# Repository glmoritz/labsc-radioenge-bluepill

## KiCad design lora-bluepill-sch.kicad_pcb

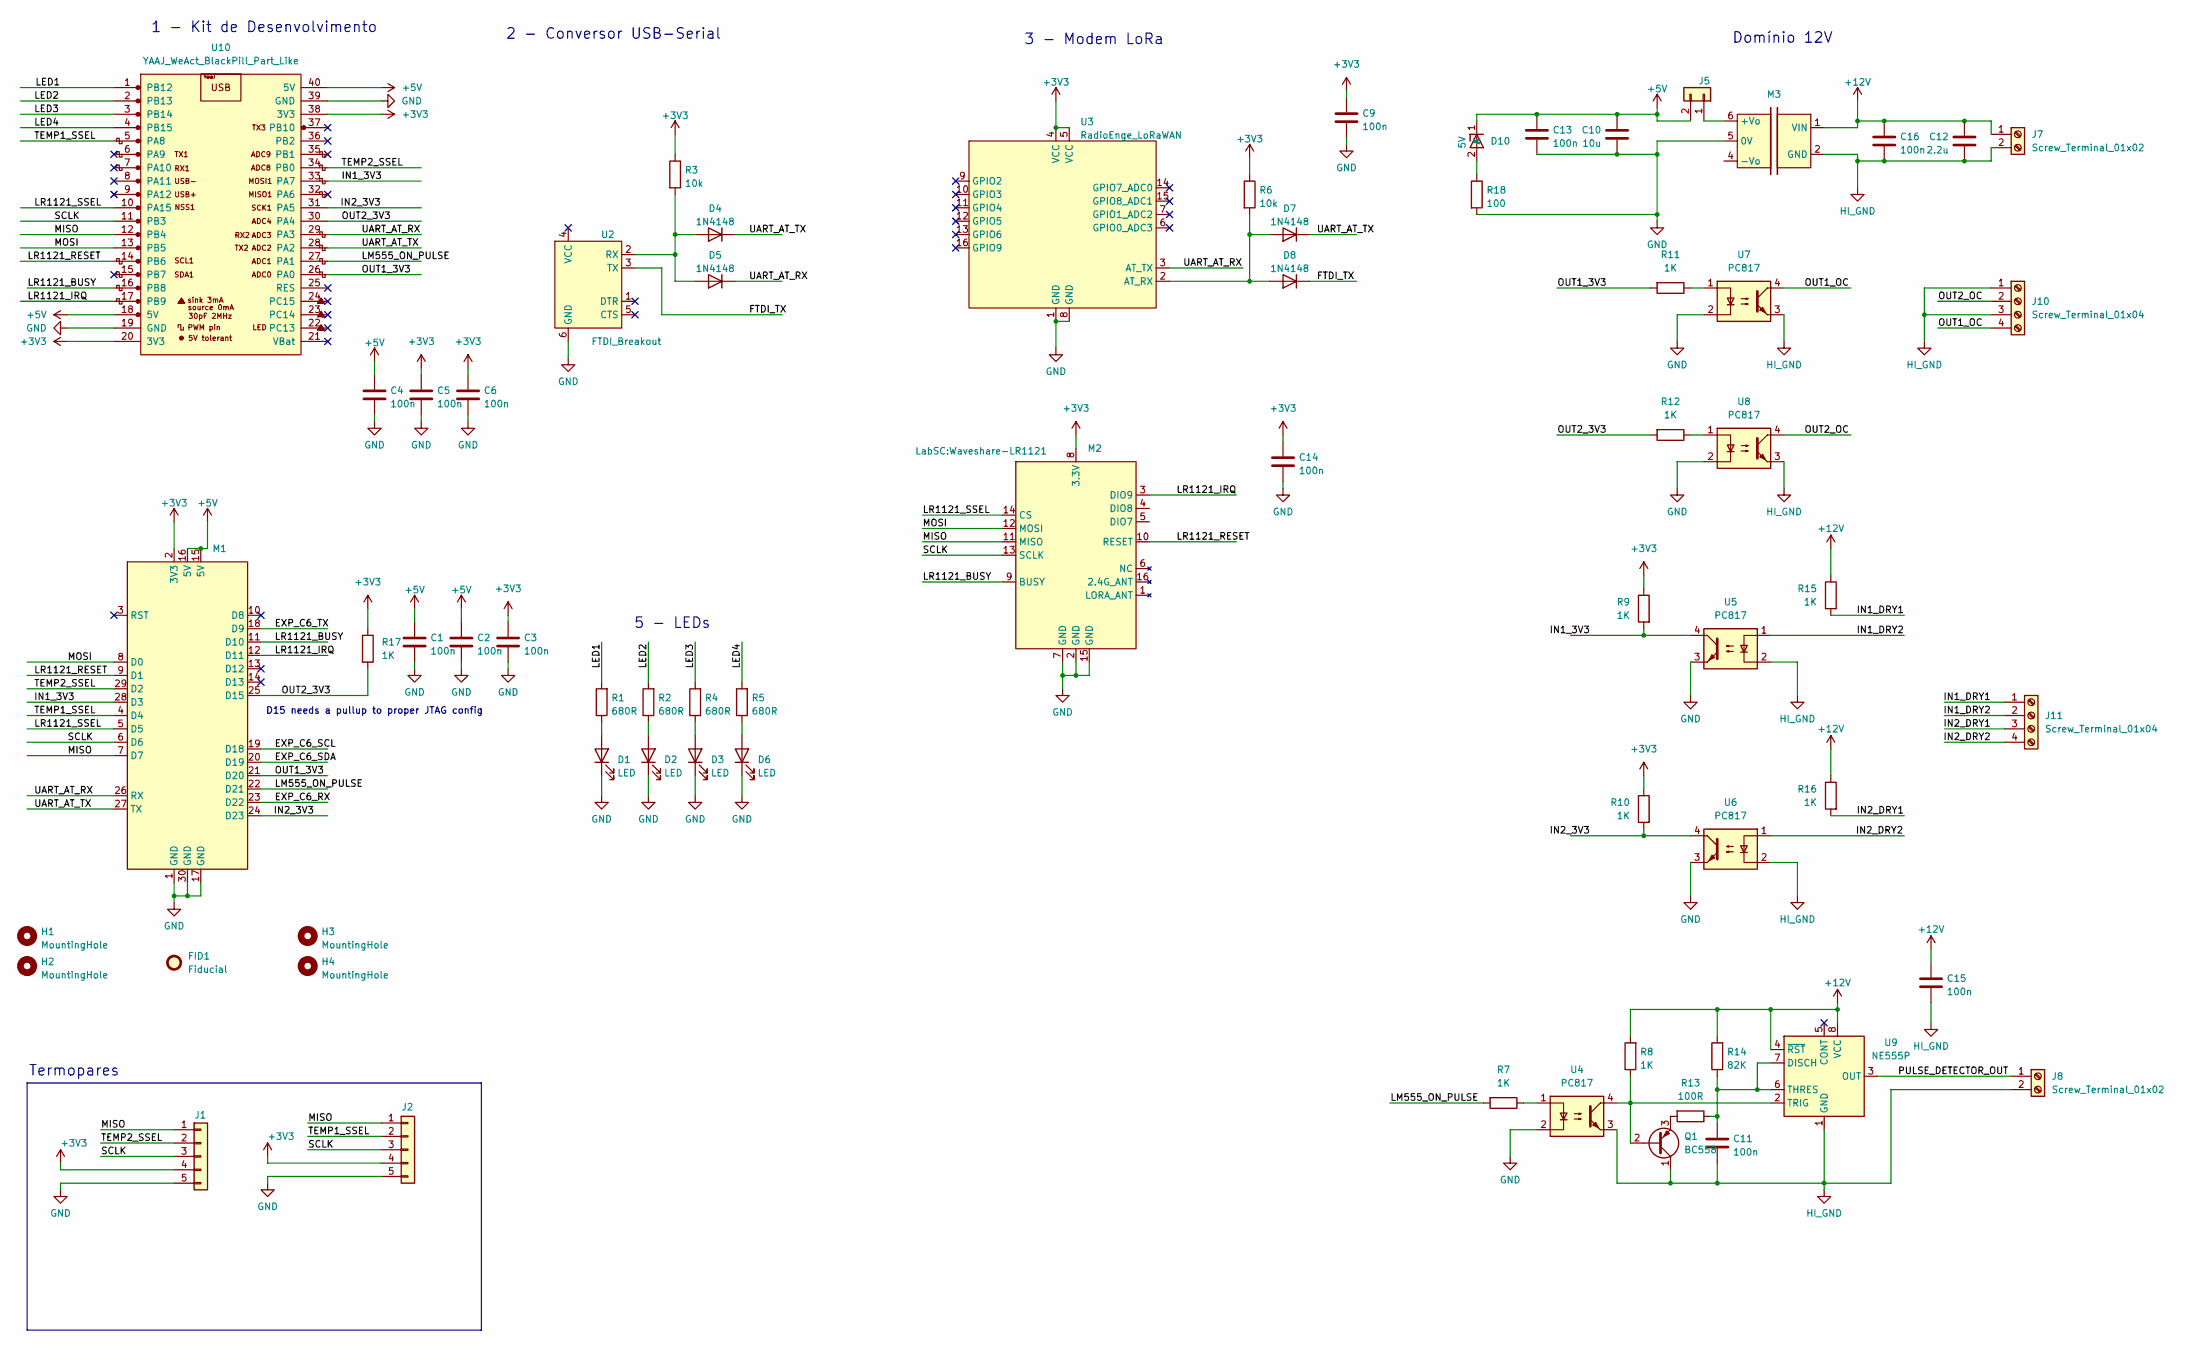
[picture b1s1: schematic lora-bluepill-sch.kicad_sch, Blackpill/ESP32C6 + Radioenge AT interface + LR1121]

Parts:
C1, C2, C3, C4, C5, C6, C9, C11, C13, C14, C15, C16: 100n; C_Disc_D6.0mm_W4.4mm_P5.00mm
C10: 10u; CP_Radial_D5.0mm_P2.50mm
C12: 2.2u; CP_Radial_D5.0mm_P2.50mm
D1, D2, D3, D6: LED; LED_D3.0mm
D4, D5, D7, D8: 1N4148; D_DO-35_SOD27_P7.62mm_Horizontal
D10: 5V; D_DO-35_SOD27_P7.62mm_Horizontal
FID1: Fiducial; labsc-logo
H1, H2, H3, H4: MountingHole; MountingHole_2.2mm_M2_DIN965
J1, J2: Conn_01x05; PinHeader_1x05_P2.54mm_Horizontal
J5: Conn_01x02; PinHeader_1x02_P2.54mm_Vertical
J7, J8: Screw_Terminal_01x02; HANDSON_KF301-2P
J10, J11: Screw_Terminal_01x04; HANDSON_KF301-4P
M1: ESP32C6-Minimal
M2: Waveshare-LR1121
M3: A1205S-2W
Q1: BC558; TO-92_Inline
R1, R2, R4, R5: 680R; R_Axial_DIN0204_L3.6mm_D1.6mm_P7.62mm_Horizontal
R3, R6: 10k; R_Axial_DIN0204_L3.6mm_D1.6mm_P7.62mm_Horizontal
R7, R8, R9, R10, R11, R12, R15, R16, R17: 1K; R_Axial_DIN0204_L3.6mm_D1.6mm_P7.62mm_Horizontal
R13: 100R; R_Axial_DIN0204_L3.6mm_D1.6mm_P7.62mm_Horizontal
R14: 82K; R_Axial_DIN0204_L3.6mm_D1.6mm_P7.62mm_Horizontal
R18: 100; R_Axial_DIN0204_L3.6mm_D1.6mm_P7.62mm_Horizontal
U2: FTDI_Breakout; PinSocket_1x06_P2.54mm_Vertical
U3: RadioEnge_LoRaWAN; LoRaModuleRadioenge
U4, U5, U6, U7, U8: PC817; DIP-4_W7.62mm
U9: NE555P; DIP-8_W7.62mm
U10: YAAJ_WeAct_BlackPill_Part_Like; YAAJ_WeAct_BlackPill_2

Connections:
+3V3: C3.1, C5.1, C6.1, C9.1, C14.1, J1.4, J2.4, M1.2 (3V3), M2.8 (3.3V), R3.1, R6.1, R9.1, R10.1, R17.1, U3.4 (VCC), U3.5 (VCC), U10.20 (3V3), U10.38 (3V3)
+5V: C1.1, C2.1, C4.1, C10.1, C13.1, D10.1 (K), J5.2, M1.15 (5V), M1.16 (5V), U10.18 (5V), U10.40 (5V)
+12V: C12.1, C15.1, C16.1, J7.1, M3.1 (VIN), R8.2, R14.2, R15.1, R16.1, U9.4 (~RST), U9.8 (VCC)
/EXP_C6_RX: M1.23 (D22)
/EXP_C6_SCL: M1.19 (D18)
/EXP_C6_SDA: M1.20 (D19)
/EXP_C6_TX: M1.18 (D9)
/FTDI_TX: D8.1 (K), U2.3 (TX)
/IN1_3V3: M1.28 (D3), R9.2, U5.4, U10.33 (PA7)
/IN1_DRY1: J11.1, R15.2
/IN1_DRY2: J11.2, U5.1
/IN2_3V3: M1.24 (D23), R10.2, U6.4, U10.31 (PA5)
/IN2_DRY1: J11.3, R16.2
/IN2_DRY2: J11.4, U6.1
/LED1: R1.2, U10.1 (PB12)
/LED2: R2.2, U10.2 (PB13)
/LED3: R4.2, U10.3 (PB14)
/LED4: R5.2, U10.4 (PB15)
/LM555_ON_PULSE: M1.22 (D21), R7.2, U10.27 (PA1)
/LR1121_BUSY: M1.11 (D10), M2.9 (BUSY), U10.16 (PB8)
/LR1121_IRQ: M1.12 (D11), M2.3 (DIO9), U10.17 (PB9)
/LR1121_RESET: M1.9 (D1), M2.10 (RESET), U10.14 (PB6)
/LR1121_SSEL: M1.5 (D5), M2.14 (CS), U10.10 (PA15)
/MISO: J1.1, J2.1, M1.7 (D7), M2.11 (MISO), U10.12 (PB4)
/MOSI: M1.8 (D0), M2.12 (MOSI), U10.13 (PB5)
/OUT1_3V3: M1.21 (D20), R11.2, U10.26 (PA0)
/OUT1_OC: J10.4, U7.4
/OUT2_3V3: M1.25 (D15), R12.2, R17.2, U10.30 (PA4)
/OUT2_OC: J10.2, U8.4
/PULSE_DETECTOR_OUT: J8.1, U9.3 (OUT)
/SCLK: J1.3, J2.3, M1.6 (D6), M2.13 (SCLK), U10.11 (PB3)
/TEMP1_SSEL: J2.2, M1.4 (D4), U10.5 (PA8)
/TEMP2_SSEL: J1.2, M1.29 (D2), U10.34 (PB0)
/UART_AT_RX: D5.1 (K), M1.26 (RX), U3.3 (AT_TX), U10.29 (PA3)
/UART_AT_TX: D4.1 (K), D7.1 (K), M1.27 (TX), U10.28 (PA2)
GND: C1.2, C2.2, C3.2, C4.2, C5.2, C6.2, C9.2, C10.2, C13.2, C14.2, D1.1 (K), D2.1 (K), D3.1 (K), D6.1 (K), J1.5, J2.5, M1.1 (GND), M1.17 (GND), M1.30 (GND), M2.2 (GND), M2.7 (GND), M2.15 (GND), M3.5 (0V), R18.2, U2.6 (GND), U3.1 (GND), U3.8 (GND), U4.2, U5.3, U6.3, U7.2, U8.2, U10.19 (GND), U10.39 (GND)
HI_GND: C11.2, C12.2, C15.2, C16.2, J7.2, J8.2, J10.1, J10.3, M3.2 (GND), Q1.1 (C), U4.3, U5.2, U6.2, U7.3, U8.3, U9.1 (GND)
unnamed: D1.2 (A), R1.1
unnamed: D2.2 (A), R2.1
unnamed: D3.2 (A), R4.1
unnamed: D4.2 (A), D5.2 (A), R3.2, U2.2 (RX)
unnamed: D6.2 (A), R5.1
unnamed: D7.2 (A), D8.2 (A), R6.2, U3.2 (AT_RX)
unnamed: D10.2 (A), R18.1
unnamed: J5.1, M3.6 (+Vo)
unnamed: Q1.2 (B), R8.1, U4.4, U9.2 (TRIG)
unnamed: Q1.3 (E), R13.2
unnamed: R7.1, U4.1
unnamed: R11.1, U7.1
unnamed: R12.1, U8.1
unnamed: C11.1, R13.1, R14.1, U9.6 (THRES), U9.7 (DISCH)

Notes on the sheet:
5 - LEDs
3 - Modem LoRa
Domínio 12V
Termopares
2 - Conversor USB-Serial
1 - Kit de Desenvolvimento
D15 needs a pullup to proper JTAG config

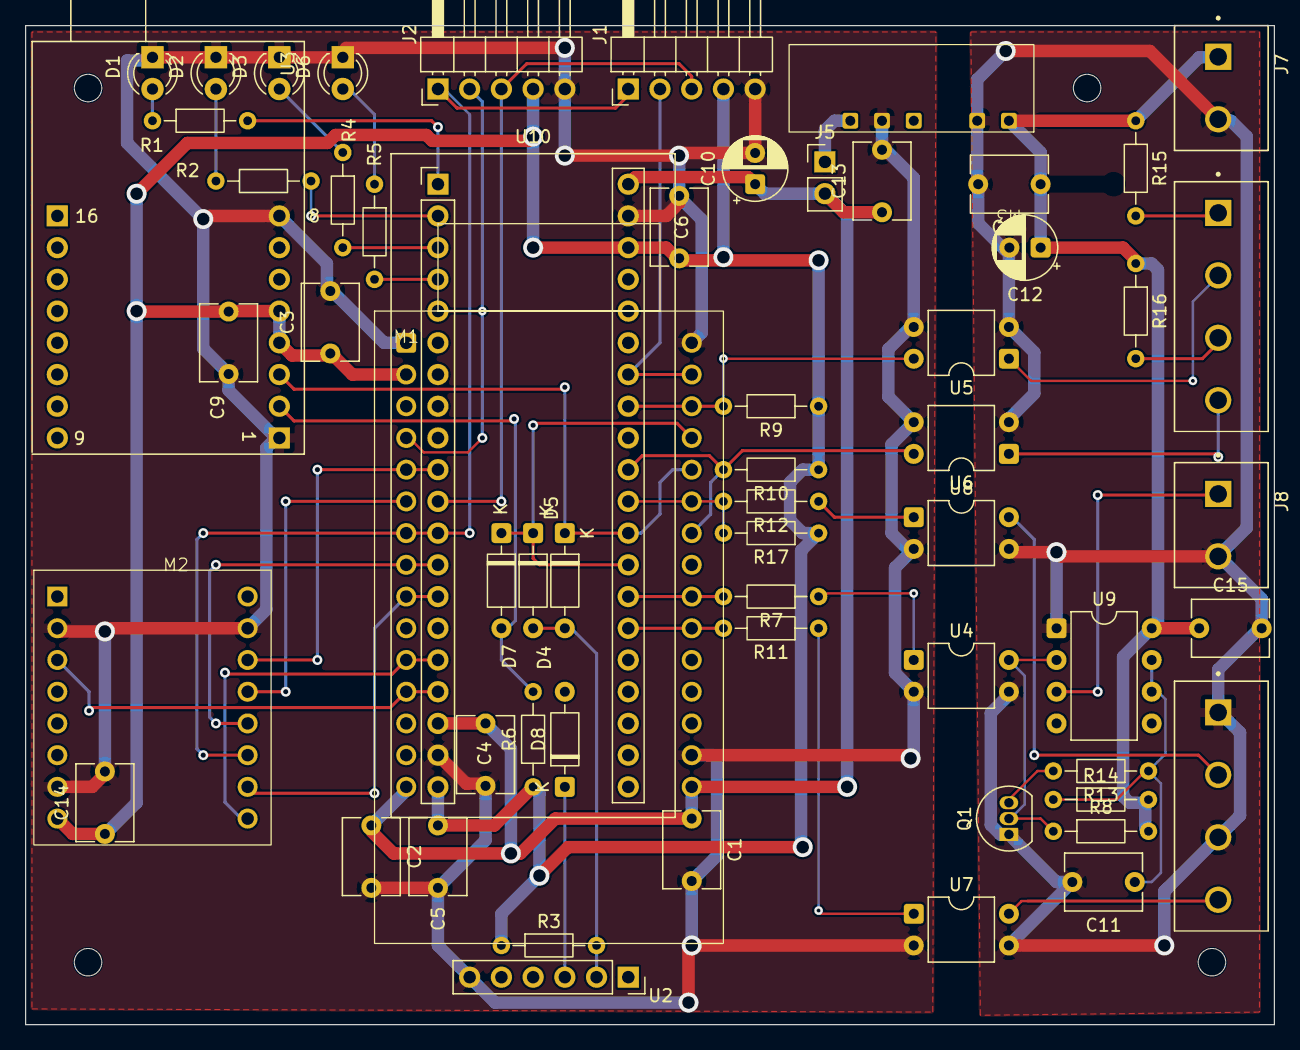
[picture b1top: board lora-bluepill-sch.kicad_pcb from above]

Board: 2 copper layers, 100.0 x 80.0 mm, 64 parts (1 on the bottom side), 46 nets.

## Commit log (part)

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2022-11-29 First Version
2022-12-01 Version sent to Fabrication
2022-12-01 added zip file to fabrication
2022-12-01 moved files
2024-09-03 removed missing library
2024-09-03 add new library
